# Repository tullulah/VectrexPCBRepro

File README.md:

# VectrexPCBRepro
OpenHardware project to reproduce the original PCB of the Vectrex (3GE Revision)

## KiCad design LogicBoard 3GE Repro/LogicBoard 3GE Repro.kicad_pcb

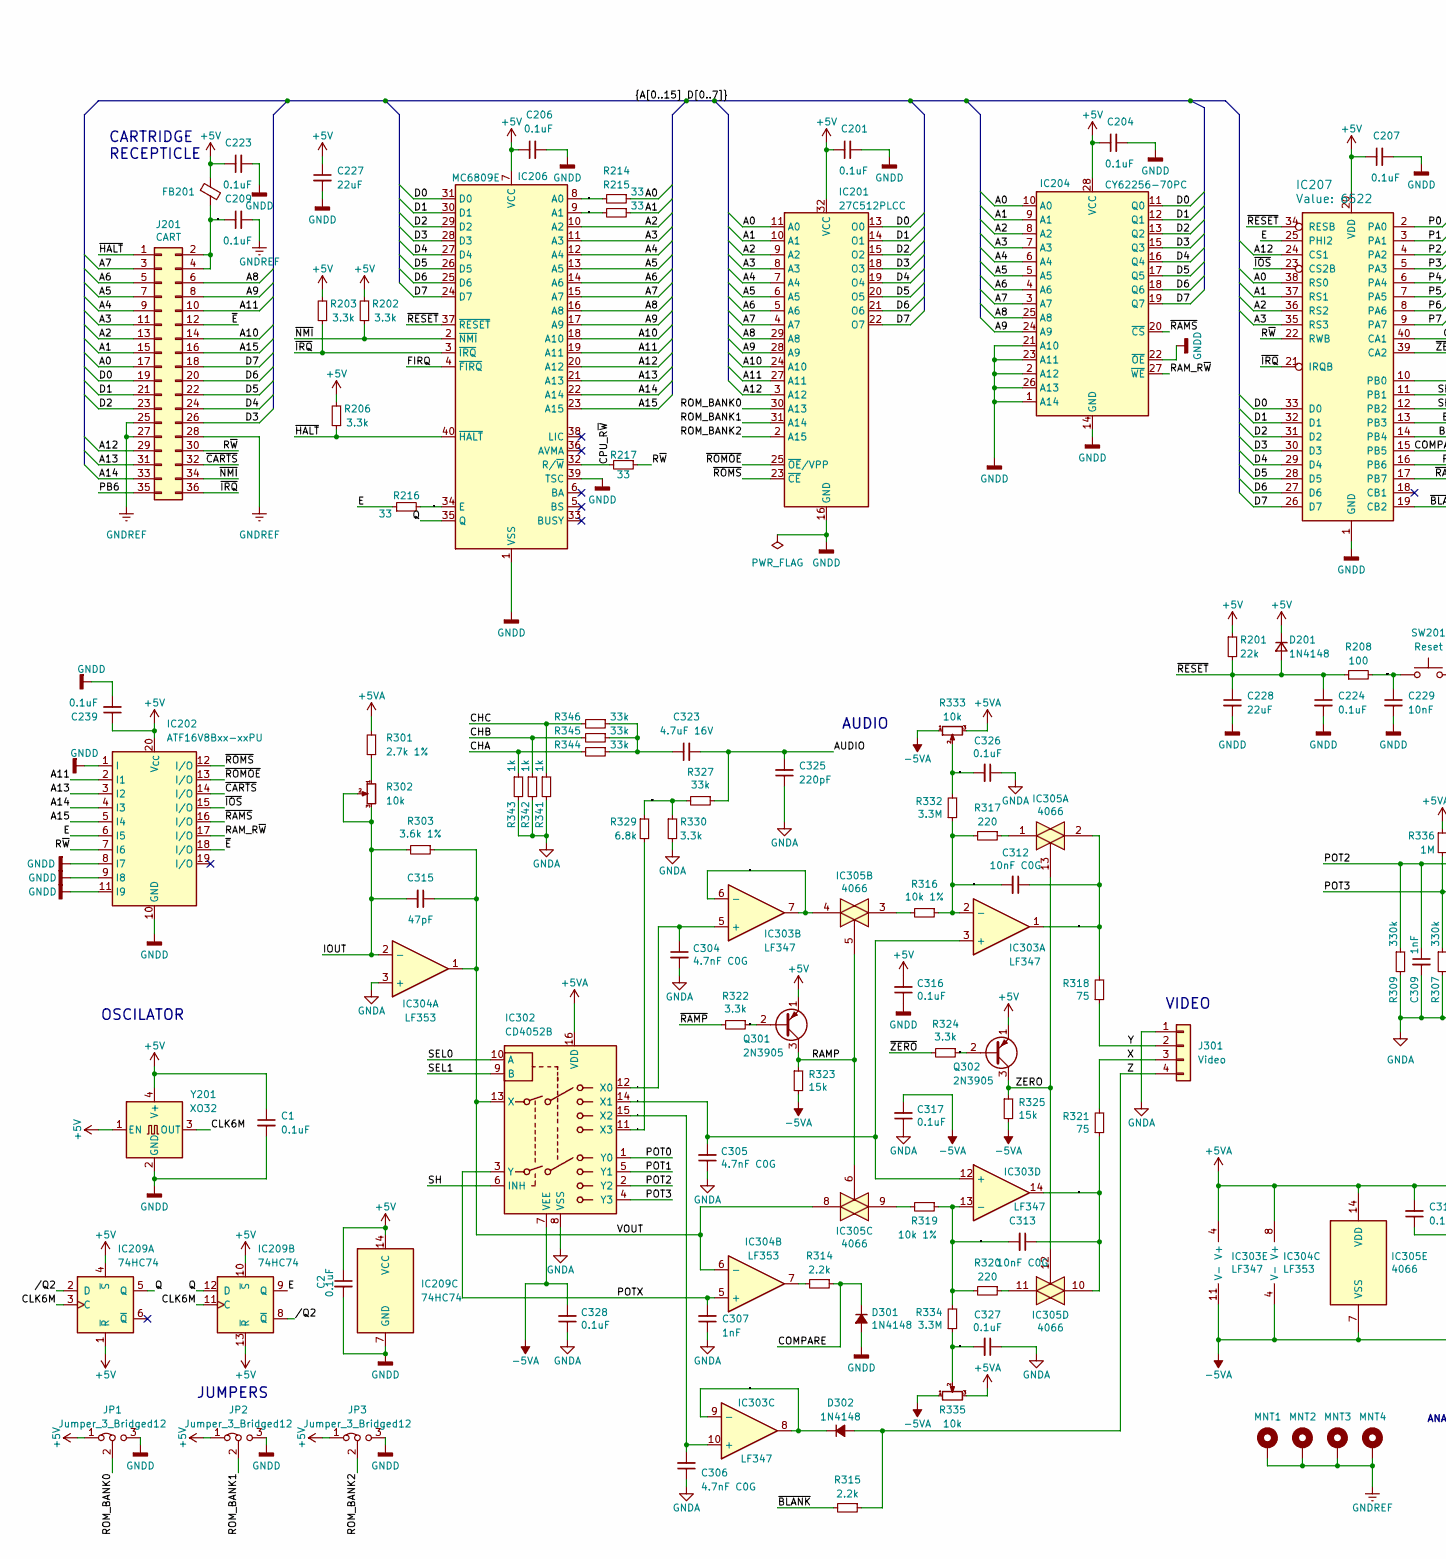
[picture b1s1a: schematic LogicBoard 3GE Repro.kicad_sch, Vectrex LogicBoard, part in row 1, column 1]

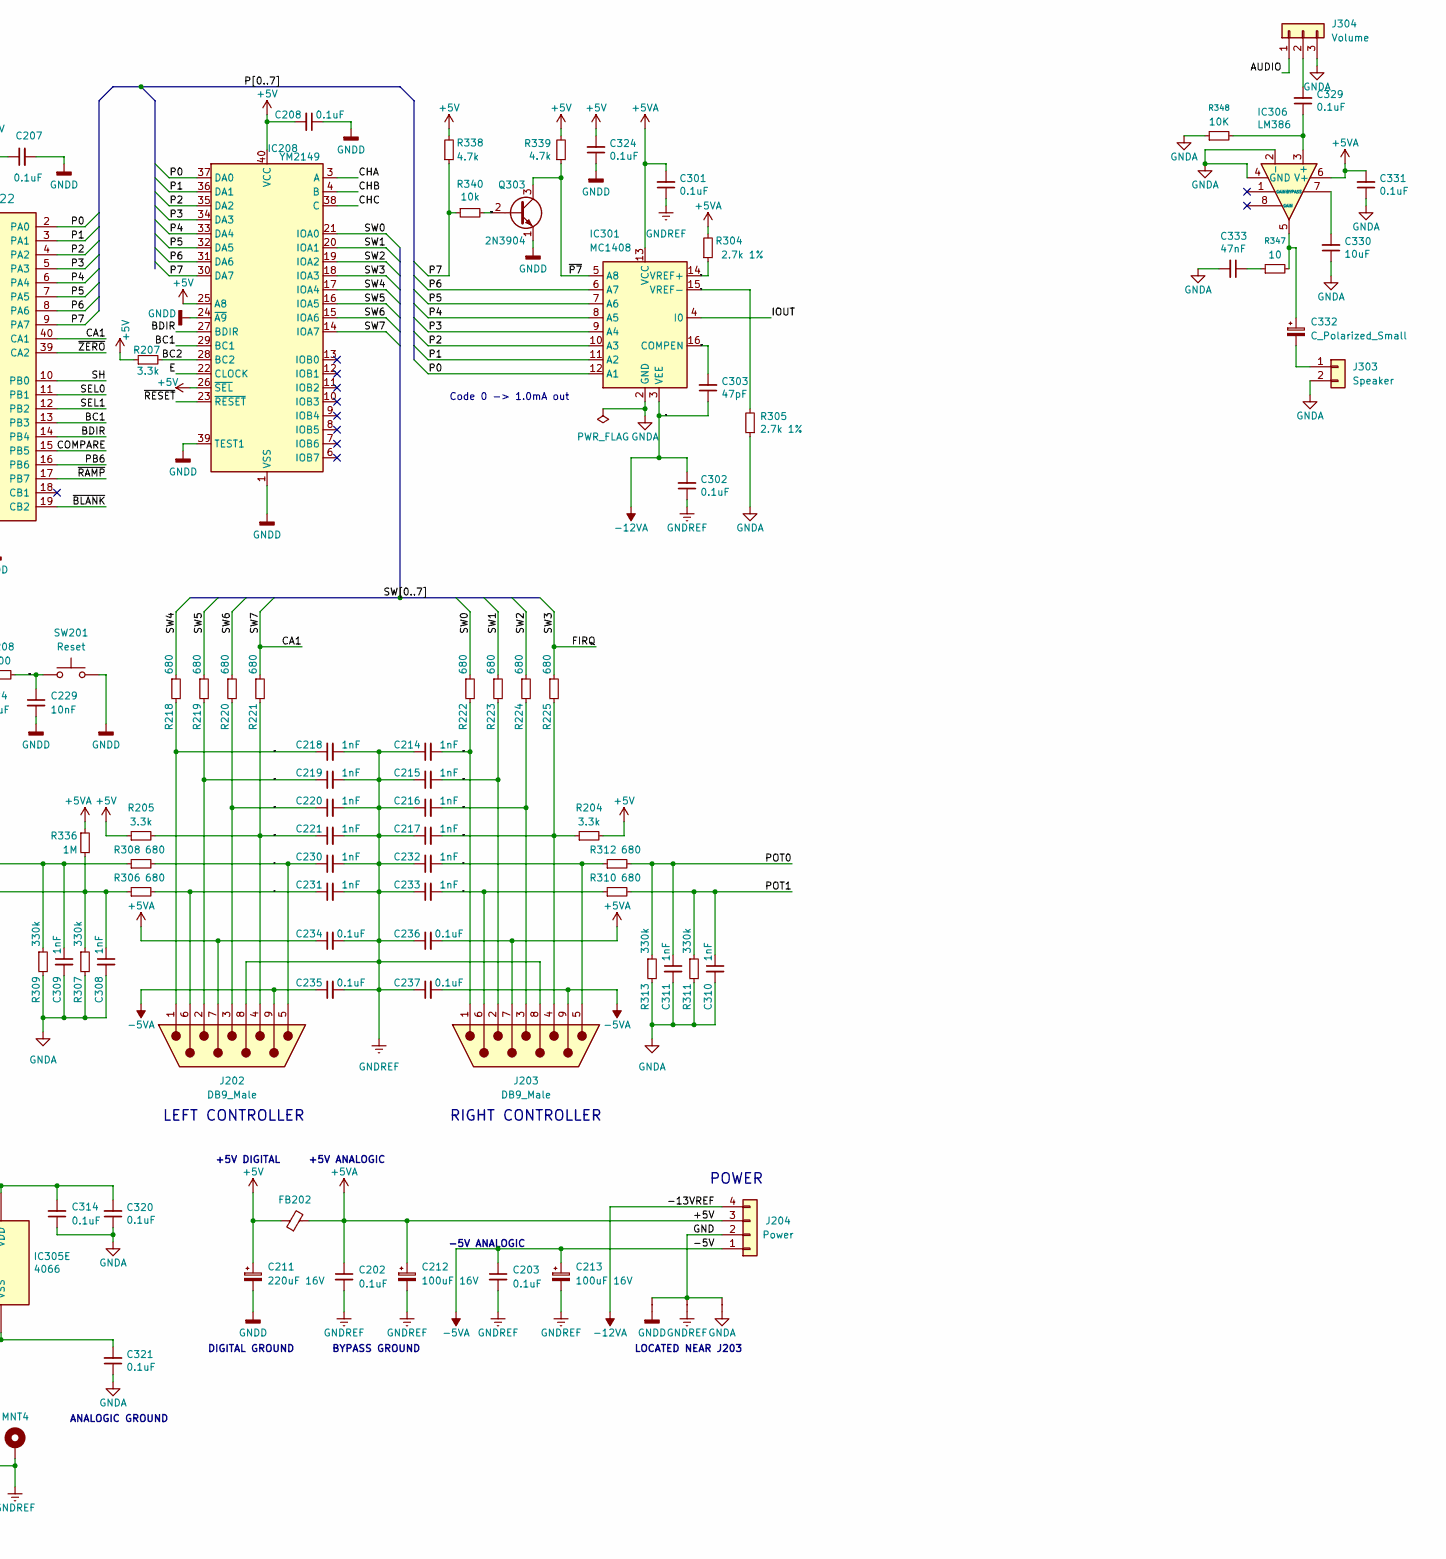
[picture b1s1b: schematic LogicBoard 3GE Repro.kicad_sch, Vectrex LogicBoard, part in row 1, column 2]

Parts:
C1, C2, C202, C203, C224, C234, C235, C236, C237, C239: 0.1uF; C_0402_1005Metric
C201, C204, C206, C207, C208, C209, C223, C301, C302, C314, C316, C317, C320, C321, C324, C326, C327, C328, C329, C331: 0.1uF; C_0402_1005Metric; Mouser 581-SR215C104k
C211: 220uF 16V; CP_Elec_8x10.5
C212, C213: 100uF 16V; CP_Elec_6.3x7.7
C214, C215, C216, C217, C218, C219, C220, C221, C230, C231, C232, C233: 1nF; C_0402_1005Metric
C227, C228: 22uF; C_1206_3216Metric
C229: 10nF; C_0402_1005Metric
C303, C315: 47pF; C_0402_1005Metric; Mouser 581-SR211A470JAR
C304, C305, C306: 4.7nF C0G; C_0603_1608Metric; Mouser 810-FG28C0G2A472JRT6
C307, C308, C309, C310, C311: 1nF; C_0402_1005Metric; Mouser 581-SR211A102JAR
C312, C313: 10nF C0G; C_0603_1608Metric; Mouser 810-FG28C0G2A103JRT6
C323: 4.7uF 16V; C_0805_2012Metric
C325: 220pF; C_0402_1005Metric; Mouser 581-SR211A221JAATR
C330: 10uF; C_0402_1005Metric; Mouser 581-SR215C104k
C332: C_Polarized_Small; CP_Elec_8x10.5
C333: 47nF; C_0402_1005Metric; Mouser 581-SR215C104k
D201: 1N4148; D_SOD-123
D301, D302: 1N4148; D_SOD-123; Mouser 512-1N4148
FB201, FB202: 96Ω @ 25MHz; L_0805_2012Metric; Mouser 623-2743007112
IC201: 27C512PLCC; PLCC-32_THT-Socket
IC202: ATF16V8Bxx-xxPU; SOIC-20W_7.5x12.8mm_P1.27mm
IC204: CY62256-70PC; SOP-28_8.4x18.16mm_P1.27mm
IC206: MC6809E; PLCC-44_SMD-Socket
IC207: 6522; PLCC-44_SMD-Socket; Mouser 955-W65C22S6TPG-14
IC208: YM2149; DIP-40_W15.24mm_Socket
IC209: 74HC74; SOIC-14_3.9x8.7mm_P1.27mm
IC301: MC1408; SOIC-16_3.9x9.9mm_P1.27mm; Mouser 926-DAC0808LCN/NOPB
IC302: CD4052B; SOIC-16_3.9x9.9mm_P1.27mm; Mouser 595-CD4052BE
IC303: LF347; SOIC-14_3.9x8.7mm_P1.27mm; Mouser 595-LF347N
IC304: LF353; SOIC-8_3.9x4.9mm_P1.27mm; Mouser 595-LF353P
IC305: 4066; SOIC-14_3.9x8.7mm_P1.27mm; Mouser 595-CD4066BE
IC306: LM386; SOIC-8_3.9x4.9mm_P1.27mm
J201: CART; SULLINS_EBC18DRAS; Mouser 587-395-036
J202, J203: DB9_Male; DSUB-9_Male_Horizontal_Vectrex
J204: Power; Molex_KK-396_A-41791-0004_1x04_P3.96mm_Vertical
J301: Video; Molex_KK-254_AE-6410-04A_1x04_P2.54mm_Vertical
J303: Speaker; PinHeader_1x02_P2.54mm_Vertical
J304: Volume; PinHeader_1x03_P2.54mm_Vertical
JP1, JP2, JP3: Jumper_3_Bridged12; PinHeader_1x03_P2.54mm_Vertical
MNT1, MNT2, MNT3, MNT4: MountingHole_Pad; MountingHole_3.5mm_Pad
Q301, Q302: 2N3905; SOT-23
Q303: 2N3904; SOT-23; Mouser 512-2N3904TA
R201: 22k; R_0402_1005Metric
R202, R203, R206, R207, R322, R324: 3.3k; R_0402_1005Metric; Mouser 603-CFR-25JR-523k3
R204, R205: 3.3k; R_0402_1005Metric
R208: 100; R_0402_1005Metric
R214, R215, R216, R217: 33; R_0402_1005Metric; Mouser 603-CFR-25JR-5233R
R218, R219, R220, R221, R222, R223, R224, R225, R306, R308, R310, R312: 680; R_0402_1005Metric
R301, R304, R305: 2.7k 1%; R_0402_1005Metric; Mouser 603-MFR-25FRF522k49
R302: 10k; Potentiometer_Bourns_3296W_Vertical; Mouser 531-PT10H-5k-S
R303: 3.6k 1%; R_0402_1005Metric; Mouser 603-MFR-25FRF52-2k61
R307, R309, R311, R313: 330k; R_0402_1005Metric; Mouser 603-CFR-25JR-52-330k
R314, R315: 2.2k; R_0402_1005Metric; Mouser 603-CFR-25JR-522k2
R316, R319: 10k 1%; R_0402_1005Metric; Mouser 603-MFR-25FRF5210k
R317, R320: 220; R_0402_1005Metric; Mouser 603-CFR-25JR-52220R
R318, R321: 75; R_0402_1005Metric; Mouser 603-MFR-25FTE52-3M3
R323, R325: 15k; R_0402_1005Metric; Mouser 603-CFR-25JR-5215k
R327, R344, R345, R346: 33k; R_0402_1005Metric; Mouser 603-CFR-25JR-52-33k
R329: 6.8k; R_0402_1005Metric; Mouser 603-CFR-25JR-52-33k
R330: 3.3k; R_0402_1005Metric; Mouser 603-CFR-25JR-52-33k
R332, R334: 3.3M; R_0402_1005Metric; Mouser 603-MFR-25FTE52-3M3
R333, R335: 10k; Potentiometer_Bourns_3296W_Vertical; Mouser 531-PT10H-10k-S
R336: 1M; R_0402_1005Metric; Mouser 603-CFR-25JR-52-330k
R338, R339: 4.7k; R_0402_1005Metric; Mouser 603-CFR-25JR-524k7
R340: 10k; R_0402_1005Metric; Mouser 603-CFR-25JR-5210k
R341, R342, R343: 1k; R_0402_1005Metric; Mouser 603-CFR-25JR-521k
R347: 10; R_0402_1005Metric
R348: 10K; R_0402_1005Metric
SW201: Reset; PinHeader_1x02_P2.54mm_Vertical
W1, W2, W3: W; NetTie-2_SMD_Pad0.5mm
Y201: XO32; Oscillator_SMD_EuroQuartz_XO32-4Pin_3.2x2.5mm

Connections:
+5V: C1.1, C2.1, C201.1, C202.1, C204.1, C206.1, C207.1, C208.2, C211.1, C212.1, C223.1, C227.1, C234.1, C236.2, C239.1, C301.2, C314.2, C316.2, C320.2, C324.2, C331.2, D201.1 (K), FB201.1, FB202.1, FB202.2, IC201.32 (VCC), IC202.20 (V_{CC}), IC204.28 (VCC), IC206.7 (VCC), IC207.20 (VDD), IC208.25 (A8), IC208.26 (~SEL), IC208.40 (VCC), IC209.1 (~R), IC209.4 (~S), IC209.10 (~S), IC209.13 (~R), IC209.14 (VCC), IC301.13 (VCC), IC302.16 (VDD), IC303.4 (V+), IC304.8 (V+), IC305.14 (VDD), IC306.6 (V+), J202.7, J203.7, J204.3, JP1.1 (A), JP2.1 (A), JP3.1 (A), Q301.1 (E), Q302.1 (E), R201.1, R202.2, R203.2, R204.2, R205.1, R206.2, R207.1, R301.2, R304.2, R333.3, R335.3, R336.1, R338.2, R339.2, Y201.1 (EN), Y201.4 (V+)
-5VA: C203.1, C213.1, C235.1, C237.2, C317.2, C321.2, C328.2, IC302.7 (VEE), IC303.11 (V-), IC304.4 (V-), IC305.7 (VSS), J202.9, J203.9, J204.1, R323.2, R325.2, R333.1, R335.1
-12VA: C302.2, C303.1, IC301.3 (VEE), J204.4
/+5V_CART: C209.1, FB201.2, J201.2, J201.4
/A0: IC201.11 (A0), IC204.10 (A0), IC207.38 (RS0), J201.17, R214.1
/A1: IC201.10 (A1), IC204.9 (A1), IC207.37 (RS1), J201.15, R215.1
/A2: IC201.9 (A2), IC204.8 (A2), IC206.10 (A2), IC207.36 (RS2), J201.13
/A3: IC201.8 (A3), IC204.7 (A3), IC206.11 (A3), IC207.35 (RS3), J201.11
/A4: IC201.7 (A4), IC204.6 (A4), IC206.12 (A4), J201.9
/A5: IC201.6 (A5), IC204.5 (A5), IC206.13 (A5), J201.7
/A6: IC201.5 (A6), IC204.4 (A6), IC206.14 (A6), J201.5
/A7: IC201.4 (A7), IC204.3 (A7), IC206.15 (A7), J201.3
/A8: IC201.29 (A8), IC204.25 (A8), IC206.16 (A8), J201.6
/A9: IC201.28 (A9), IC204.24 (A9), IC206.17 (A9), J201.8
/A10: IC201.24 (A10), IC206.18 (A10), J201.14
/A11: IC201.27 (A11), IC202.2 (I1), IC206.19 (A11), J201.10
/A12: IC201.3 (A12), IC206.20 (A12), IC207.24 (CS1), J201.29
/A13: IC202.3 (I2), IC206.21 (A13), J201.31
/A14: IC202.4 (I3), IC206.22 (A14), J201.33
/A15: IC202.5 (I4), IC206.23 (A15), J201.16
/AUDIO: C323.2, C325.2, J304.1, R327.1
/BC1: IC207.13 (PB3), IC208.29 (BC1)
/BC2: IC208.28 (BC2), R207.2
/BDIR: IC207.14 (PB4), IC208.27 (BDIR)
/CHA: IC208.3 (A), R343.1, R344.2
/CHB: IC208.4 (B), R342.1, R345.2
/CHC: IC208.38 (C), R341.1, R346.2
/CLK6M: IC209.3 (C), IC209.11 (C), Y201.3 (OUT)
/COMPARE: D301.1 (K), IC207.15 (PB5), R314.1
/COMPEN: C303.2, IC301.16 (COMPEN)
/CPU_A0: IC206.8 (A0), R214.2
/CPU_A1: IC206.9 (A1), R215.2
/CPU_E: IC206.34 (E), R216.2
/CPU_R~W: IC206.32 (R/~W), R217.2
/D0: IC201.13 (O0), IC204.11 (Q0), IC206.31 (D0), IC207.33 (D0), J201.19
/D1: IC201.14 (O1), IC204.12 (Q1), IC206.30 (D1), IC207.32 (D1), J201.21
/D2: IC201.15 (O2), IC204.13 (Q2), IC206.29 (D2), IC207.31 (D2), J201.23
/D3: IC201.18 (O3), IC204.15 (Q3), IC206.28 (D3), IC207.30 (D3), J201.26
/D4: IC201.19 (O4), IC204.16 (Q4), IC206.27 (D4), IC207.29 (D4), J201.24
/D5: IC201.20 (O5), IC204.17 (Q5), IC206.26 (D5), IC207.28 (D5), J201.22
/D6: IC201.21 (O6), IC204.18 (Q6), IC206.25 (D6), IC207.27 (D6), J201.20
/D7: IC201.22 (O7), IC204.19 (Q7), IC206.24 (D7), IC207.26 (D7), J201.18
/DIGITAL_AUDIO: R327.2, R329.1, R330.1
/E: IC202.6 (I5), IC207.25 (PHI2), IC208.22 (CLOCK), IC209.9 (Q), R216.1
/GND: J204.2, W1.2, W2.2, W3.2
/IC303A_FB: C312.2, IC303.2 (-), R316.1, R317.2, R332.1
/IC303A_Y: C312.1, IC303.1, IC305.2, R318.2
/IC303B_FB: IC303.6 (-), IC303.7, IC305.4
/IC303C_FB: D302.1 (K), IC303.8, IC303.9 (-)
/IC303D_FB: C313.2, IC303.13 (-), R319.1, R320.2, R334.2
/IC303D_X: C313.1, IC303.14, IC305.10, R321.1
/IOUT: C315.2, IC301.4 (I0), IC304.2 (-), R302.2, R302.3, R303.2
/J202_B1: C218.1, J202.1, R218.2
/J202_B2: C219.1, J202.2, R219.2
/J202_B3: C220.1, J202.3, R220.2
/J202_B4: C221.1, J202.4, R205.2, R221.2
/J202_X: C230.1, J202.5, R308.2
/J202_Y: C231.1, J202.6, R306.2
/J203_B1: C214.2, J203.1, R222.2
/J203_B2: C215.2, J203.2, R223.2
/J203_B3: C216.2, J203.3, R224.2
/J203_B4: C217.2, J203.4, R204.1, R225.2
/J203_X: C232.2, J203.5, R312.1
/J203_Y: C233.2, J203.6, R310.1
/P0: IC207.2 (PA0), IC208.37 (DA0), IC301.12 (A1)
/P1: IC207.3 (PA1), IC208.36 (DA1), IC301.11 (A2)
/P2: IC207.4 (PA2), IC208.35 (DA2), IC301.10 (A3)
/P3: IC207.5 (PA3), IC208.34 (DA3), IC301.9 (A4)
/P4: IC207.6 (PA4), IC208.33 (DA4), IC301.8 (A5)
/P5: IC207.7 (PA5), IC208.32 (DA5), IC301.7 (A6)
/P6: IC207.8 (PA6), IC208.31 (DA6), IC301.6 (A7)
/P7: IC207.9 (PA7), IC208.30 (DA7), R338.1, R340.1
/PB6: IC207.16 (PB6), J201.35
/POT0: C311.1, IC302.1 (Y0), R312.2, R313.1
/POT1: C310.1, IC302.5 (Y1), R310.2, R311.1
/POT2: C309.1, IC302.2 (Y2), R308.1, R309.1
/POT3: C308.1, IC302.4 (Y3), R306.1, R307.1, R336.2
/POTX: C307.2, IC302.3 (Y), IC304.5 (+)
/Q: IC206.35 (Q), IC209.5 (Q), IC209.12 (D)
/Q301_BASE: Q301.2 (B), R322.1
/Q302_BASE: Q302.2 (B), R324.1
/Q303_BASE: Q303.2 (B), R340.2
/RAMP: IC305.5, IC305.6, Q301.3 (C), R323.1
/RAM_R~W: IC202.17 (I/O), IC204.27 (~WE)
/ROM_BANK0: IC201.30 (A13), JP1.2 (C)
/ROM_BANK1: IC201.31 (A14), JP2.2 (C)
/ROM_BANK2: IC201.2 (A15), JP3.2 (C)
/R~W: IC202.7 (I6), IC207.22 (RWB), J201.30, R217.1
/SEL0: IC207.11 (PB1), IC302.10 (A)
/SEL1: IC207.12 (PB2), IC302.9 (B)
/SH: IC207.10 (PB0), IC302.6 (INH)
/SW0: IC208.21 (IOA0), R222.1
/SW1: IC208.20 (IOA1), R223.1
/SW2: IC208.19 (IOA2), R224.1
/SW3: IC206.4 (~FIRQ), IC208.18 (IOA3), R225.1
/SW4: IC208.17 (IOA4), R218.1
/SW5: IC208.16 (IOA5), R219.1
/SW6: IC208.15 (IOA6), R220.1
/SW7: IC207.40 (CA1), IC208.14 (IOA7), R221.1
/SWITCH_RESET: C229.1, R208.2, SW201.1
/VOUT: C315.1, IC302.13 (X), IC304.1, IC304.6 (-), IC305.8, R303.1
/VREF+: IC301.14 (VREF+), R304.1
/VREF-: IC301.15 (VREF-), R305.2
/X: J301.3, R321.2
/X0: C304.1, IC302.12 (X0), IC303.5 (+)
/X1: C305.2, IC302.14 (X1), IC303.3 (+), IC303.12 (+)
/X2: C306.2, IC302.15 (X2), IC303.10 (+)
/X3: IC302.11 (X3), R329.2
/X_OFFSET: C327.2, R334.1, R335.2
/Y: J301.2, R318.1
/Y_OFFSET: C326.2, R332.2, R333.2
/Z: D302.2 (A), J301.4, R315.1
/ZERO: IC305.12, IC305.13, Q302.3 (C), R325.1
//Q2: IC209.2 (D), IC209.8 (~Q)
/~BLANK: IC207.19 (CB2), R315.2
/~CARTS: IC202.14 (I/O), J201.32
/~E: IC202.18 (I/O), J201.12
/~HALT: IC206.40 (~HALT), J201.1, R206.1
/~IOS: IC202.15 (I/O), IC207.23 (CS2B)
/~IRQ: IC206.3 (~IRQ), IC207.21 (IRQB), J201.36, R203.1
/~NMI: IC206.2 (~NMI), J201.34, R202.1
/~P7: IC301.5 (A8), Q303.3 (C), R339.1
/~RAMP: IC207.17 (PB7), R322.2
/~RAMS: IC202.16 (I/O), IC204.20 (~CS)
/~RESET: C224.1, C228.1, D201.2 (A), IC206.37 (~RESET), IC207.34 (RESB), IC208.23 (~RESET), R201.2, R208.1
/~ROMOE: IC201.25 (~OE/VPP), IC202.13 (I/O)
/~ROMS: IC201.23 (~CE), IC202.12 (I/O)
/~ZERO: IC207.39 (CA2), R324.2
GNDA: C304.2, C305.1, C306.1, C307.1, C308.2, C309.2, C310.2, C311.2, C314.1, C317.1, C320.1, C321.1, C325.1, C326.1, C327.1, C328.1, C330.1, C331.1, C333.2, IC301.2 (GND), IC302.8 (VSS), IC304.3 (+), IC306.2 (-), IC306.4 (GND), J301.1, J303.2, J304.3, R305.1, R307.2, R309.2, R311.2, R313.2, R330.2, R341.2, R342.2, R343.2, R348.1, W3.1
GNDD: C1.2, C2.2, C201.2, C204.2, C206.2, C207.2, C208.1, C211.2, C223.2, C224.2, C227.2, C228.2, C229.2, C239.2, C316.1, C324.1, D301.2 (A), IC201.16 (GND), IC202.1 (I), IC202.8 (I7), IC202.9 (I8), IC202.10 (GND), IC202.11 (I9), IC204.1 (A14), IC204.2 (A12), IC204.14 (GND), IC204.21 (A10), IC204.22 (~OE), IC204.23 (A11), IC204.26 (A13), IC206.1 (VSS), IC206.39 (TSC), IC207.1 (GND), IC208.1 (VSS), IC208.24 (~A9), IC208.39 (TEST1), IC209.7 (GND), JP1.3 (B), JP2.3 (B), JP3.3 (B), Q303.1 (E), SW201.2, W1.1, Y201.2 (GND)
GNDREF: C202.2, C203.2, C209.2, C212.2, C213.2, C214.1, C215.1, C216.1, C217.1, C218.2, C219.2, C220.2, C221.2, C230.2, C231.2, C232.1, C233.1, C234.2, C235.2, C236.1, C237.1, C301.1, C302.1, J201.25, J201.27, J201.28, J202.8, J203.8, MNT1.1 (1_1), MNT2.1 (1_1), MNT3.1 (1_1), MNT4.1 (1_1), W2.1
unnamed: C323.1, R344.1, R345.1, R346.1
unnamed: C332.1, IC306.5, R347.2
unnamed: C333.1, R347.1
unnamed: IC304.7, R314.2
unnamed: IC305.1, R317.1
unnamed: IC305.3, R316.2
unnamed: IC305.9, R319.2
unnamed: IC305.11, R320.1
unnamed: C329.1, IC306.3 (+), R348.2
unnamed: C330.2, IC306.7 (BYPASS)
unnamed: C332.2, J303.1
unnamed: C329.2, J304.2
unnamed: R301.1, R302.1

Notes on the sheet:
LOCATED NEAR J203
OSCILATOR
DIGITAL GROUND
+5V DIGITAL
AUDIO
BYPASS GROUND
CARTRIDGE RECEPTICLE
-5V ANALOGIC
VIDEO
POWER
+5V ANALOGIC
ANALOGIC GROUND
RIGHT CONTROLLER
Code 0 -> 1.0mA out
JUMPERS
LEFT CONTROLLER

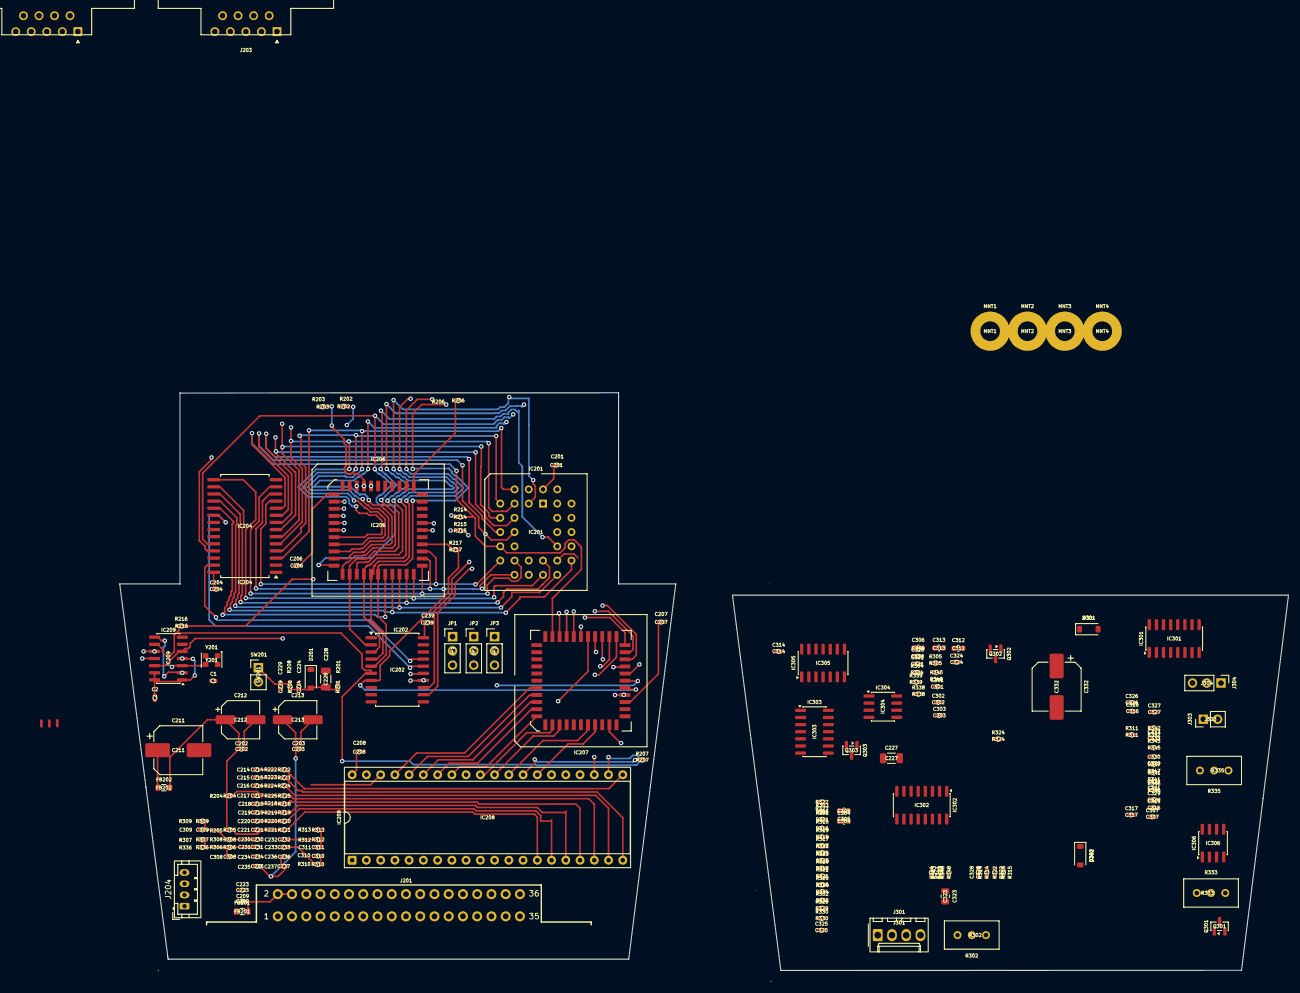
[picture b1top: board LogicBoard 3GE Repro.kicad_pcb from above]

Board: 4 copper layers, 208.4 x 105.0 mm, 169 parts (0 on the bottom side), 144 nets.

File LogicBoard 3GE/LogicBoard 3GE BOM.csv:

Reference;Value;Datasheet;Footprint;Qty;DNP
"C1,C202,C203,C204,C206,C207,C208,C209,C223,C224,C225,C226,C234,C235,C236,C237,C301,C302,C314,C316,C317,C320,C321,C324,C326,C327,C328,""0.1uF"",""~"",""Capacitor_SMD:C_0805_2012Metric"",""27"",""""";;;;;
"C2,C116,""0.1uF 50V"",""~"",""Capacitor_SMD:C_0805_2012Metric"",""2"",""""";;;;;
"C106,""0.22nF"",""~"",""Capacitor_SMD:C_0805_2012Metric"",""1"",""""";;;;;
"C113,C238,""10uF 16V"",""~"",""-- mixed values --"",""2"",""""";;;;;
"C114,C211,""220uF 16V"",""~"",""-- mixed values --"",""2"",""""";;;;;
"C210,C222,""20pF"",""~"",""Capacitor_SMD:C_0805_2012Metric"",""2"",""""";;;;;
"C212,C213,""100uF 16V"",""~"",""Capacitor_Tantalum_SMD:CP_EIA-3528-15_AVX-H"",""2"",""""";;;;;
"C214,C215,C216,C217,C218,C219,C220,C221,C230,C231,C232,C233,C307,C308,C309,C310,C311,""1nF"",""~"",""Capacitor_SMD:C_0805_2012Metric"",""17"",""""";;;;;
"C227,""22uF"",""~"",""Capacitor_Tantalum_SMD:CP_EIA-3528-15_AVX-H"",""1"",""""";;;;;
"C228,""22uF 16V"",""~"",""Capacitor_Tantalum_SMD:CP_EIA-3528-15_AVX-H"",""1"",""""";;;;;
"C229,C304,C305,C306,C312,C313,""10nF"",""~"",""-- mixed values --"",""6"",""""";;;;;
"C303,C315,""47pF"",""~"",""Capacitor_SMD:C_0805_2012Metric"",""2"",""""";;;;;
"C323,""4.7uF 16V"",""~"",""Capacitor_Tantalum_SMD:CP_EIA-3528-15_AVX-H"",""1"",""""";;;;;
"C325,""220pF"",""~"",""Capacitor_SMD:C_0805_2012Metric"",""1"",""""";;;;;
"D201,D301,D302,""1N4148"",""~"",""Diode_SMD:D_SOD-323"",""3"",""""";;;;;
"IC103,""LM386-3"","""",""Package_SO:SOIC-8-1EP_3.9x4.9mm_P1.27mm_EP2.29x3mm"",""1"",""""";;;;;
"IC201,""27C512PLCC"",""http://ww1.microchip.com/downloads/en/DeviceDoc/doc0015.pdf"",""Package_LCC:PLCC-32_11.4x14.0mm_P1.27mm"",""1"",""""";;;;;
"IC202,""74LS00"",""http://www.ti.com/lit/gpn/sn74ls00"",""Package_SO:SOIC-14_3.9x8.7mm_P1.27mm"",""1"",""""";;;;;
"IC203,""74LS32"",""http://www.ti.com/lit/gpn/sn74LS32"",""Package_SO:SOIC-14_3.9x8.7mm_P1.27mm"",""1"",""""";;;;;
"IC204,""CY62256-70PC"",""https://ecee.colorado.edu/~mcclurel/Cypress_SRAM_CY62256.pdf"",""Package_SO:SOP-28_8.4x18.16mm_P1.27mm"",""1"",""""";;;;;
"IC206,""68A09"",""http://pdf.datasheetcatalog.com/datasheet/motorola/MC68B09S.pdf"",""Package_DIP:DIP-40_W15.24mm"",""1"",""""";;;;;
"IC207,""6522"","""",""Package_DIP:DIP-40_W15.24mm"",""1"",""""";;;;;
"IC208,""AY3-8912"","""",""Package_DIP:DIP-28_W15.24mm"",""1"",""""";;;;;
"IC301,""MC1408"",""http://www.pinballpcb.com/datasheets/OnMC1408-dac.pdf"",""Package_SO:SO-16_3.9x9.9mm_P1.27mm"",""1"",""""";;;;;
"IC302,""CD4052B"",""http://www.ti.com/lit/ds/symlink/cd4052b.pdf"",""Package_SO:SO-16_3.9x9.9mm_P1.27mm"",""1"",""""";;;;;
"IC303,""LF347"",""~"",""Package_SO:SOIC-14_3.9x8.7mm_P1.27mm"",""1"",""""";;;;;
"IC304,""LF353"",""~"",""Package_SO:SOIC-8-1EP_3.9x4.9mm_P1.27mm_EP2.29x3mm"",""1"",""""";;;;;
"IC305,""4066"",""http://www.ti.com/lit/ds/symlink/cd4066b.pdf"",""Package_SO:TSSOP-14_4.4x5mm_P0.65mm"",""1"",""""";;;;;
"J103,SW201,""Conn_01x02"",""~"",""Connector_JST:JST_EH_B2B-EH-A_1x02_P2.50mm_Vertical"",""2"",""""";;;;;
"J201,""AMP 5645384-1"",""~"",""Vectrex LogicBoard:SULLINS_EBC18DRAS"",""1"",""""";;;;;
"J202,J203,""MD-90SM"","""",""MiniDin9:CUI_MD-90SM"",""2"",""""";;;;;
"J204,""Power"",""~"",""Connector_Molex:Molex_KK-396_A-41791-0004_1x04_P3.96mm_Vertical"",""1"",""""";;;;;
"J301,""Video"",""~"",""Connector_Molex:Molex_KK-254_AE-6410-04A_1x04_P2.54mm_Vertical"",""1"",""""";;;;;
"J304,""Conn_01x03_Pin"",""~"",""Connector_JST:JST_EH_B3B-EH-A_1x03_P2.50mm_Vertical"",""1"",""""";;;;;
"MNT1,MNT2,MNT3,MNT4,""MountingHole_Pad"",""~"",""MountingHole:MountingHole_3.5mm_Pad"",""4"",""""";;;;;
"Q301,Q302,""FMMT3905"",""https://www.nteinc.com/specs/original/2N3905_06.pdf"",""Package_TO_SOT_SMD:SOT-23"",""2"",""""";;;;;
"Q303,""FMMT3904"",""https://www.fairchildsemi.com/datasheets/2N/2N3904.pdf"",""Package_TO_SOT_SMD:SOT-23"",""1"",""""";;;;;
"R103,""10"",""~"",""Resistor_SMD:R_0805_2012Metric"",""1"",""""";;;;;
"R104,R329,""6.8k"",""~"",""Resistor_SMD:R_0805_2012Metric"",""2"",""""";;;;;
"R105,""47k"",""~"",""Resistor_SMD:R_0805_2012Metric"",""1"",""""";;;;;
"R201,""22k"",""~"",""Resistor_SMD:R_0805_2012Metric"",""1"",""""";;;;;
"R202,R203,R204,R205,R206,R207,R209,R210,R322,R324,R330,""3.3k"",""~"",""Resistor_SMD:R_0805_2012Metric"",""11"",""""";;;;;
"R208,""100"",""~"",""Resistor_SMD:R_0805_2012Metric"",""1"",""""";;;;;
"R214,R215,R216,R217,R226,""33"",""~"",""Resistor_SMD:R_0805_2012Metric"",""5"",""""";;;;;
"R218,R219,R220,R221,R222,R223,R224,R225,R306,R308,R310,R312,""680"",""~"",""Resistor_SMD:R_0805_2012Metric"",""12"",""""";;;;;
"R301,R304,R305,""2.7k 1%"",""~"",""Resistor_SMD:R_0805_2012Metric"",""3"",""""";;;;;
"R302,R333,R335,R340,""10k"",""~"",""-- mixed values --"",""4"",""""";;;;;
"R303,""3.6k 1%"",""~"",""Resistor_SMD:R_0805_2012Metric"",""1"",""""";;;;;
"R307,R309,R311,R313,""330k"",""~"",""Resistor_SMD:R_0805_2012Metric"",""4"",""""";;;;;
"R314,R315,""2.2k"",""~"",""Resistor_SMD:R_0805_2012Metric"",""2"",""""";;;;;
"R316,R319,""10k 1%"",""~"",""Resistor_SMD:R_0805_2012Metric"",""2"",""""";;;;;
"R317,R320,""220"",""~"",""Resistor_SMD:R_0805_2012Metric"",""2"",""""";;;;;
"R318,R321,""75"",""~"",""Resistor_SMD:R_0805_2012Metric"",""2"",""""";;;;;
"R323,R325,""15k"",""~"",""Resistor_SMD:R_0805_2012Metric"",""2"",""""";;;;;
"R327,R344,R345,R346,""33k"",""~"",""Resistor_SMD:R_0805_2012Metric"",""4"",""""";;;;;
"R332,R334,""3.3M"",""~"",""Resistor_SMD:R_0805_2012Metric"",""2"",""""";;;;;
"R336,""1M"",""~"",""Resistor_SMD:R_0805_2012Metric"",""1"",""""";;;;;
"R338,R339,""4.7k"",""~"",""Resistor_SMD:R_0805_2012Metric"",""2"",""""";;;;;
"R341,R342,R343,""1k"",""~"",""Resistor_SMD:R_0805_2012Metric"",""3"",""""";;;;;
"W1,W2,W3,""W"",""~"","""",""3"",""""";;;;;
"Y201,""6MHz"",""~"",""Crystal:Crystal_SMD_7050-2Pin_7.0x5.0mm"",""1"",""""";;;;;

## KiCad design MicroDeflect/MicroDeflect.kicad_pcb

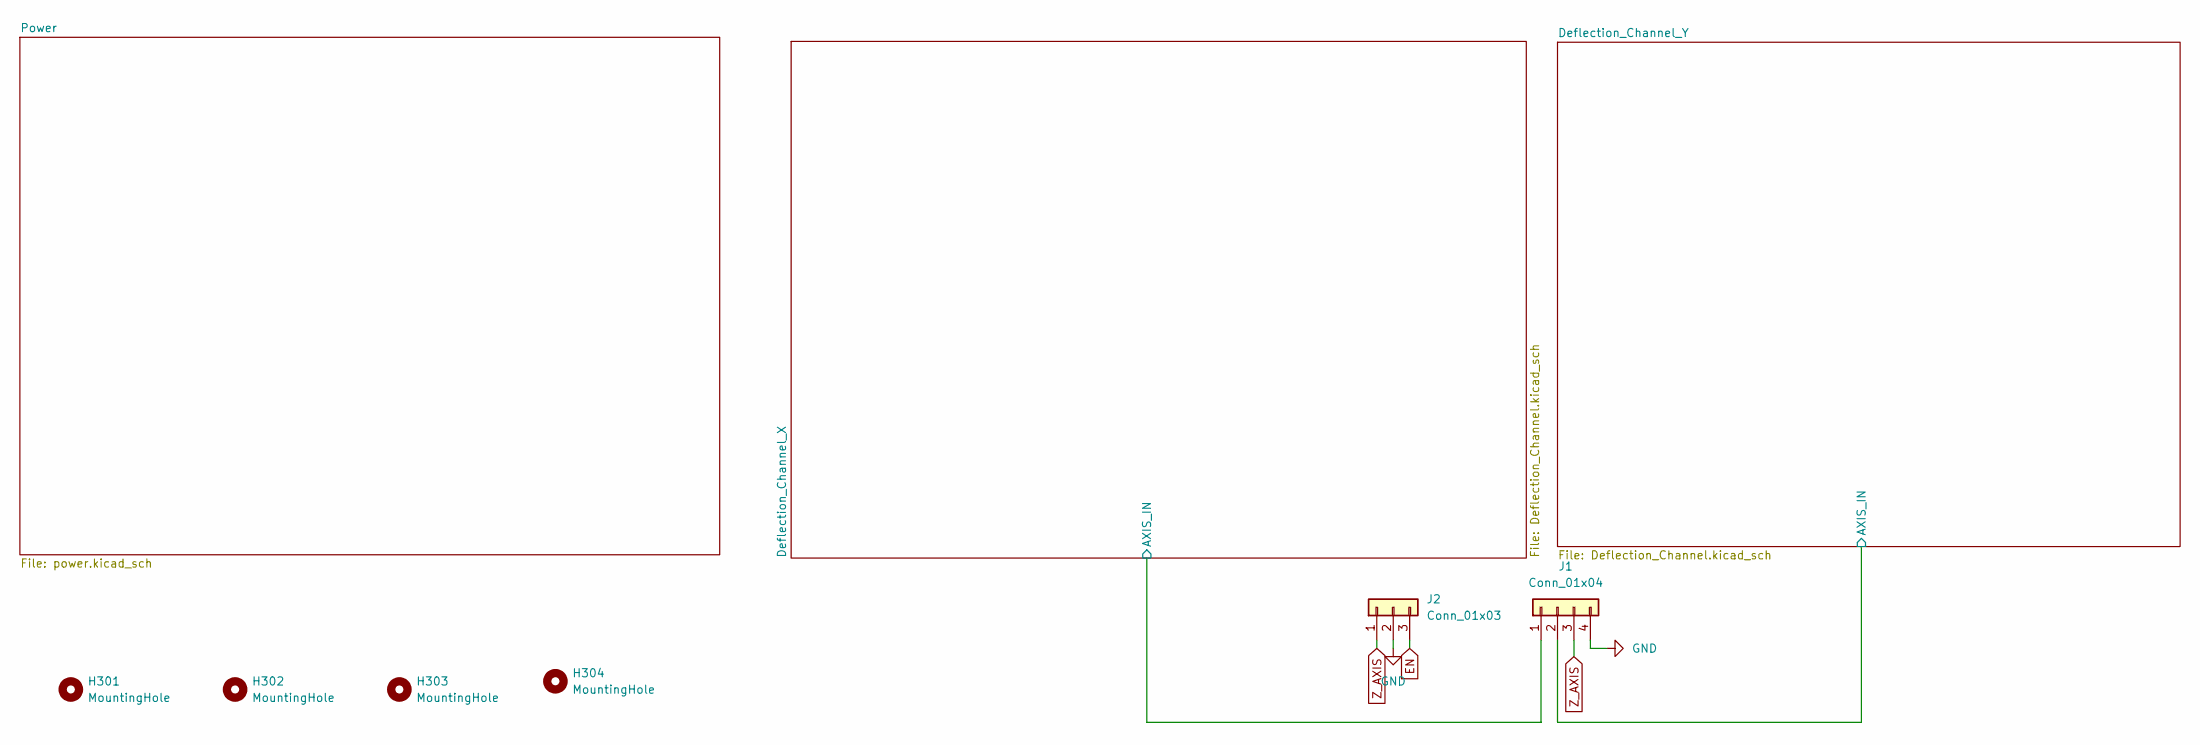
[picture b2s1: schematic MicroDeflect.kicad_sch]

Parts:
H301, H302, H303, H304: MountingHole
J1: Conn_01x04; JST_PH_B4B-PH-K_1x04_P2.00mm_Vertical
J2: Conn_01x03

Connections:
/Deflection_Channel_X/AXIS_IN: J1.1; also elsewhere on the board
/Deflection_Channel_Y/AXIS_IN: J1.2; also elsewhere on the board
EN: J2.3; also elsewhere on the board
GND: J1.4, J2.2; also elsewhere on the board
Z_AXIS: J1.3, J2.1

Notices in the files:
LogicBoard 3GE Repro/LogicBoard 3GE Repro.kicad_sch:
or send a letter to Creative Commons, PO Box 1866, Mountain View, CA 94042, USA.
To view a copy of this license, visit http://creativecommons.org/licenses/by-sa/4.0
This work is licensed under the Creative Commons
